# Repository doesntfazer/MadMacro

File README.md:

# MadMacro

 The MadMacro macro pad inspired by the game Deadlock. It has extra keys by the pinky for spells, abilities, and whatever else you would want to do with it.

# Firmware
 This keyboard runs on Vial QMK. Firmware is in the [Keyboard Dweebs Firmware repository.](https://github.com/doesntfazer/Keyboard-Dweebs-Firmware-repository/tree/main/VIAL-QMK/madmacro) Just drag and drop the UF2 file into the drive in bootloader mode.

# Supplies
| Amount    | Supplies |
| -------- | ------- |
|1x|PCB|
|1x|[Super Mini RP2040](https://www.aliexpress.us/item/3256805724197386.html?gatewayAdapt=glo2usa4itemAdapt) (Keep in mind that the RP2040 zero is compatible as well But it will not sit flush)|
|  1x |   [WS2712B 5050 RGB (Optional)](https://www.aliexpress.us/item/3256805981215355.html?spm=a2g0o.productlist.main.13.789e45z345z3Ot&algo_pvid=f2182711-468e-4bfc-85f9-2924c0640053&algo_exp_id=f2182711-468e-4bfc-85f9-2924c0640053-6&pdp_npi=4%40dis%21USD%213.02%212.83%21%21%213.02%212.83%21%402101c5c317278069022964071eed80%2112000036083321561%21sea%21US%214079175621%21X&curPageLogUid=CnNPtl0TAZz6&utparam-url=scene%3Asearch%7Cquery_from%3A)  |
| 1x |   [SN74LVC1T45 Shift register.](https://www.lcsc.com/product-detail/74-Series_TI_SN74LVC1T45QDCKRQ1_SN74LVC1T45QDCKRQ1_C139353.html) (part #C139353 on JLCPCB) (only needed if using RGB)   |
| 33x |   [Kailh hot swap sockets.](https://www.aliexpress.us/item/3256806866334888.html?spm=a2g0o.productlist.main.1.31f4XqeFXqeFxS&algo_pvid=3fc20960-6666-4636-a2ea-9c8b1fa50853&algo_exp_id=3fc20960-6666-4636-a2ea-9c8b1fa50853-0&pdp_npi=4%40dis%21USD%2114.01%216.86%21%21%2197.59%2147.82%21%402103010e17278069896855766ec269%2112000039244942221%21sea%21US%214079175621%21X&curPageLogUid=cEbphnHpUDGO&utparam-url=scene%3Asearch%7Cquery_from%3A) |
|33x|[1n4148w SOD-123 SMD diodes](https://www.aliexpress.us/item/2251832762203586.html?spm=a2g0o.productlist.main.1.b12d77ba0Z8bMR&algo_pvid=69af949b-3673-4901-ac46-df4c03523242&algo_exp_id=69af949b-3673-4901-ac46-df4c03523242-0&pdp_npi=4%40dis%21USD%212.80%212.80%21%21%212.80%212.80%21%402103080717278070240346268edcd8%2166189487480%21sea%21US%214079175621%21X&curPageLogUid=fazZvCXMgI1j&utparam-url=scene%3Asearch%7Cquery_from%3A) |
|33x|Cherry MX or compatible switches|
|4x|1.25u keycaps|
|4x|1.5u keycaps|
|25x|1u keycaps|
|1x|Plate (3d printable in the 3d Models folder in this repo)|
|1x|Bottom (3d printable in the 3d Models folder in this repo)|
|1x|Wrist rest (optional)(3d printable in the 3d Models folder in this repo)|
|4x|6x2mm magnets (Optional if using wrist rest)|
|5x|M2 screws (At least 8mm long)|

# Ordering
Send the Gerber zip in the production folder to PCBWay or JLCPCB. (There are files to have it assembled at the factory. That is up to you)

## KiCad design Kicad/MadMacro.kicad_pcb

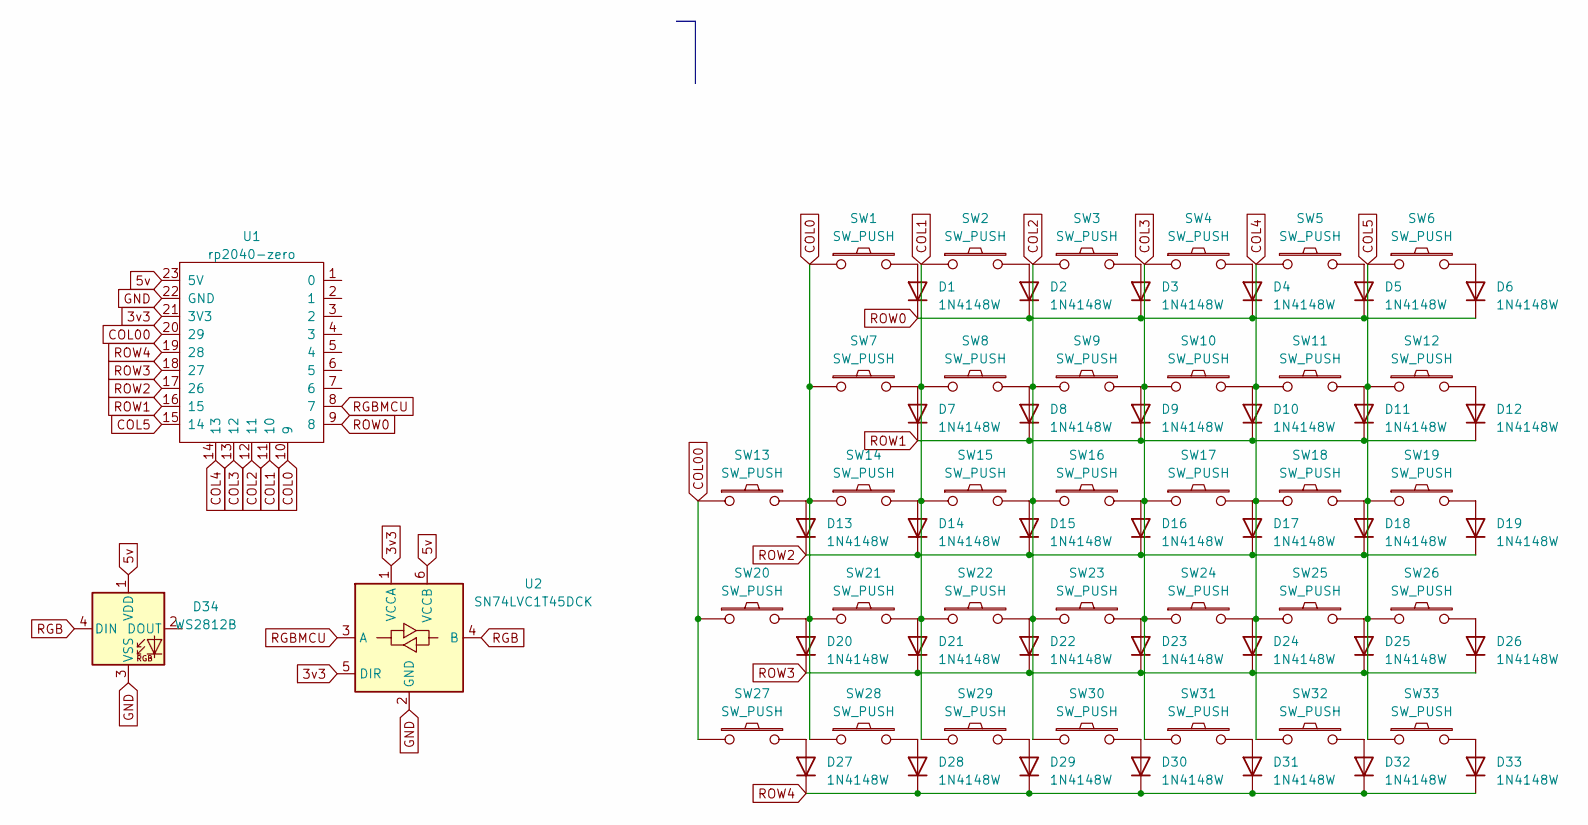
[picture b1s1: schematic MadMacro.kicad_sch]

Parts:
D1, D2, D3, D4, D5, D6, D7, D8, D9, D10, D11, D12, D13, D14, D15, D16, D17, D18, D19, D20, D21, D22, D23, D24, D25, D26, D27, D28, D29, D30, D31, D32, D33: 1N4148W; D_SOD-123
D34: WS2812B; LED_WS2812B_PLCC4_5.0x5.0mm_P3.2mm
SW1, SW2, SW3, SW4, SW5, SW6, SW8, SW9, SW10, SW11, SW12, SW13, SW15, SW16, SW17, SW18, SW19, SW20, SW22, SW23, SW24, SW25, SW26, SW27, SW29: SW_PUSH; SW_Hotswap_Kailh_MX_1.00u
SW7, SW14, SW21, SW28: SW_PUSH; SW_Hotswap_Kailh_MX_1.25u
SW30, SW31, SW32, SW33: SW_PUSH; SW_Hotswap_Kailh_MX_1.50u_90deg
U1: rp2040-zero; rp2040-zero-tht-nocut-largerpads
U2: SN74LVC1T45DCK; SOT-363_SC-70-6; LCSC C139353

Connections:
3v3: U1.21 (3V3), U2.1 (VCCA), U2.5 (DIR)
5v: D34.1 (VDD), U1.23 (5V), U2.6 (VCCB)
COL0: SW1.1, SW7.1, SW14.1, SW21.1, SW28.1, U1.10 (9)
COL00: SW13.1, SW20.1, SW27.1, U1.20 (29)
COL1: SW2.1, SW8.1, SW15.1, SW22.1, SW29.1, U1.11 (10)
COL2: SW3.1, SW9.1, SW16.1, SW23.1, SW30.1, U1.12 (11)
COL3: SW4.1, SW10.1, SW17.1, SW24.1, SW31.1, U1.13 (12)
COL4: SW5.1, SW11.1, SW18.1, SW25.1, SW32.1, U1.14 (13)
COL5: SW6.1, SW12.1, SW19.1, SW26.1, SW33.1, U1.15 (14)
GND: D34.3 (VSS), U1.22 (GND), U2.2 (GND)
unnamed: D1.2 (A), SW1.2
unnamed: D2.2 (A), SW2.2
unnamed: D3.2 (A), SW3.2
unnamed: D4.2 (A), SW4.2
unnamed: D5.2 (A), SW5.2
unnamed: D6.2 (A), SW6.2
unnamed: D7.2 (A), SW7.2
unnamed: D8.2 (A), SW8.2
unnamed: D9.2 (A), SW9.2
unnamed: D10.2 (A), SW10.2
unnamed: D11.2 (A), SW11.2
unnamed: D12.2 (A), SW12.2
unnamed: D13.2 (A), SW13.2
unnamed: D14.2 (A), SW14.2
unnamed: D15.2 (A), SW15.2
unnamed: D16.2 (A), SW16.2
unnamed: D17.2 (A), SW17.2
unnamed: D18.2 (A), SW18.2
unnamed: D19.2 (A), SW19.2
unnamed: D20.2 (A), SW20.2
unnamed: D21.2 (A), SW21.2
unnamed: D22.2 (A), SW22.2
unnamed: D23.2 (A), SW23.2
unnamed: D24.2 (A), SW24.2
unnamed: D25.2 (A), SW25.2
unnamed: D26.2 (A), SW26.2
unnamed: D27.2 (A), SW27.2
unnamed: D28.2 (A), SW28.2
unnamed: D29.2 (A), SW29.2
unnamed: D30.2 (A), SW30.2
unnamed: D31.2 (A), SW31.2
unnamed: D32.2 (A), SW32.2
unnamed: D33.2 (A), SW33.2
RGB: D34.4 (DIN), U2.4 (B)
RGBMCU: U1.8 (7), U2.3 (A)
ROW0: D1.1 (K), D2.1 (K), D3.1 (K), D4.1 (K), D5.1 (K), D6.1 (K), U1.9 (8)
ROW1: D7.1 (K), D8.1 (K), D9.1 (K), D10.1 (K), D11.1 (K), D12.1 (K), U1.16 (15)
ROW2: D13.1 (K), D14.1 (K), D15.1 (K), D16.1 (K), D17.1 (K), D18.1 (K), D19.1 (K), U1.17 (26)
ROW3: D20.1 (K), D21.1 (K), D22.1 (K), D23.1 (K), D24.1 (K), D25.1 (K), D26.1 (K), U1.18 (27)
ROW4: D27.1 (K), D28.1 (K), D29.1 (K), D30.1 (K), D31.1 (K), D32.1 (K), D33.1 (K), U1.19 (28)

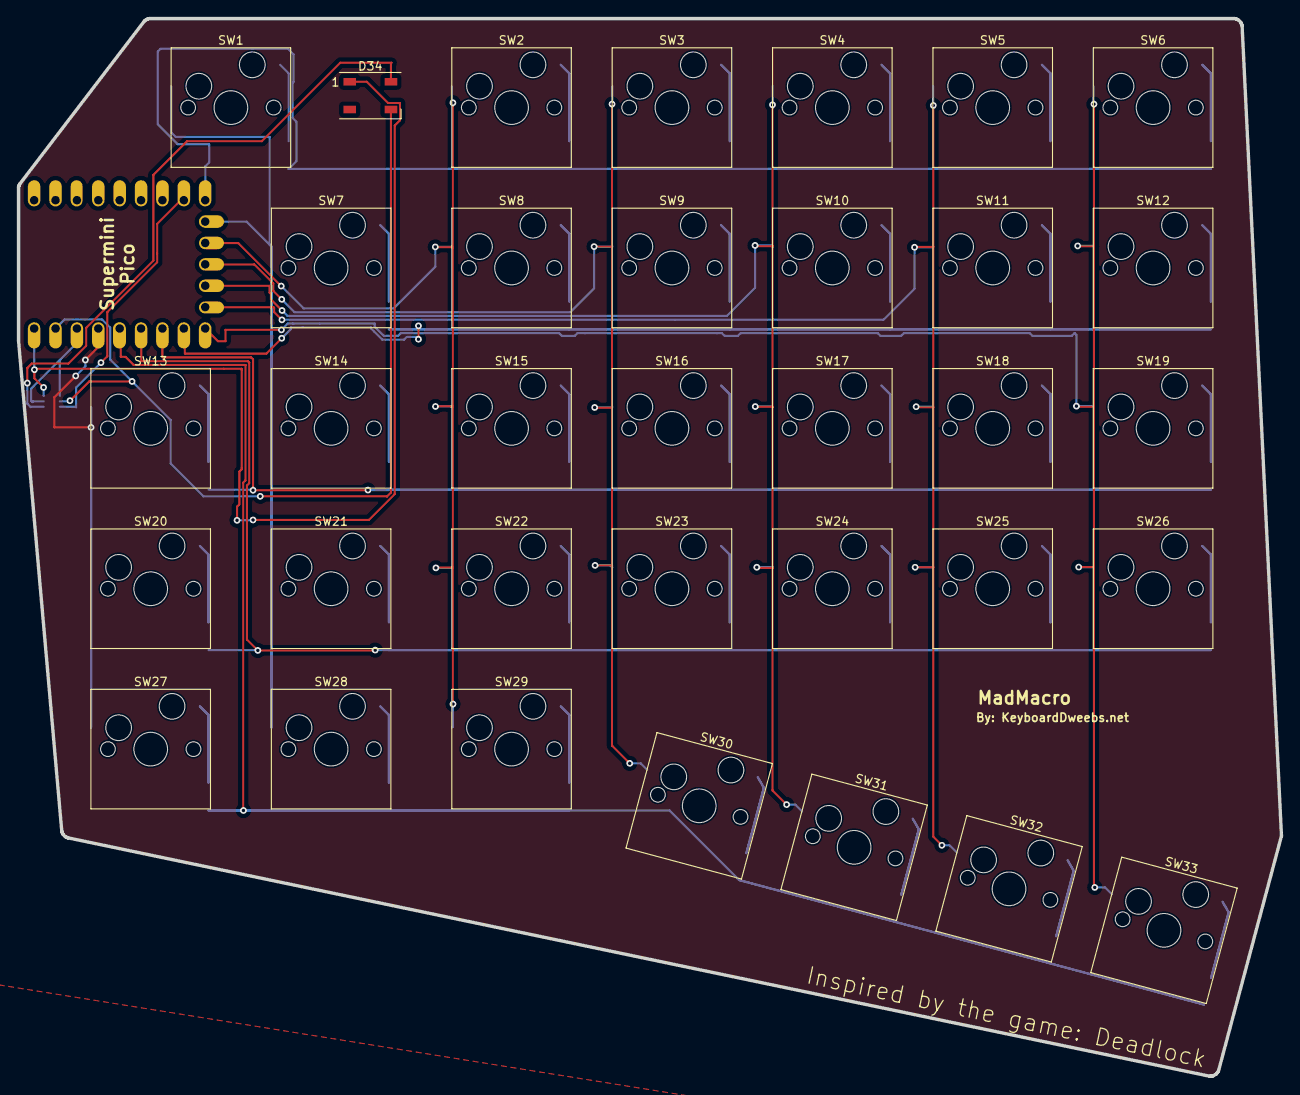
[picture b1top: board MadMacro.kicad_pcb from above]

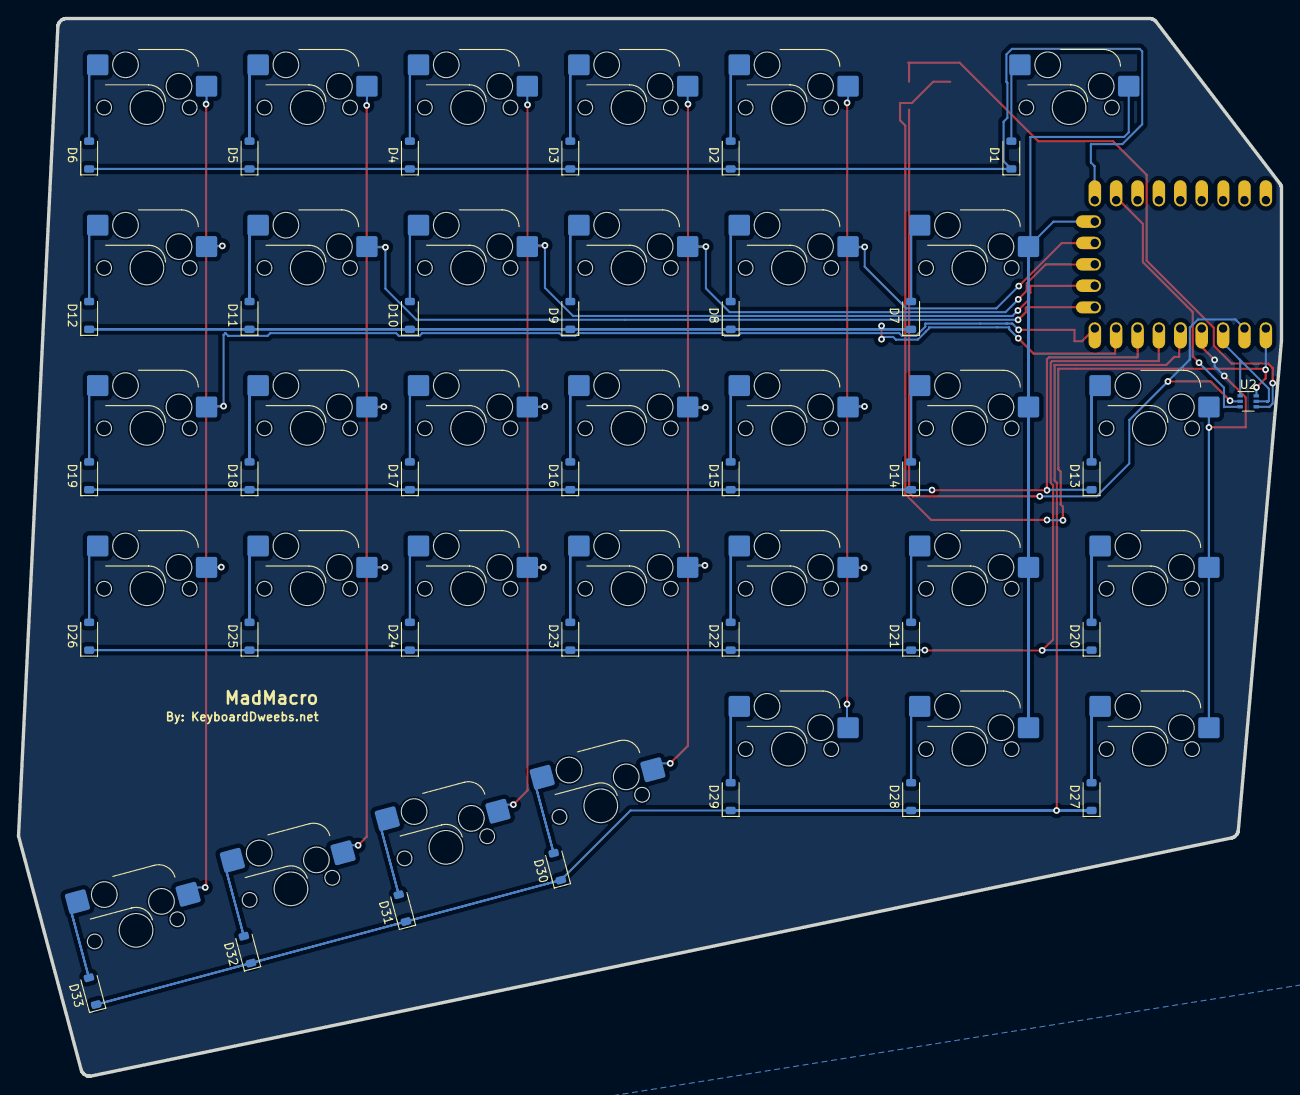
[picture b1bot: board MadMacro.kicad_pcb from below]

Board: 2 copper layers, 150.0 x 125.6 mm, 69 parts (34 on the bottom side), 50 nets.

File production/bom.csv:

Designator,Footprint,Quantity,Value,LCSC Part #
"D1, D10, D11, D12, D13, D14, D15, D16, D17, D18, D19, D2, D20, D21, D22, D23, D24, D25, D26, D27, D28, D29, D3, D30, D31, D32, D33, D4, D5, D6, D7, D8, D9",D_SOD-123,33,1N4148W,
D34,LED_WS2812B_PLCC4_5.0x5.0mm_P3.2mm,1,WS2812B,
"SW1, SW10, SW11, SW12, SW13, SW15, SW16, SW17, SW18, SW19, SW2, SW20, SW22, SW23, SW24, SW25, SW26, SW27, SW29, SW3, SW4, SW5, SW6, SW8, SW9",SW_Hotswap_Kailh_MX_1.00u,25,SW_PUSH,
"SW14, SW21, SW28, SW7",SW_Hotswap_Kailh_MX_1.25u,4,SW_PUSH,
"SW30, SW31, SW32, SW33",SW_Hotswap_Kailh_MX_1.50u_90deg,4,SW_PUSH,
U1,rp2040-zero-tht-nocut-largerpads,1,rp2040-zero,
U2,SOT-363_SC-70-6,1,SN74LVC1T45DCK,C139353

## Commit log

2024-10-01 MadMacro First Commit
    Adding Mad macro files.
